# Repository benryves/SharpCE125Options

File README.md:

# Sharp CE-125 Options

This repository describes three "option" devices that plug into the expansion port of the Sharp CE-125 printer and cassette interface:

* [ROM](rom): A simple cartridge that contains a BASIC program that can be loaded onto the pocket computer via the ROM command.
* [Keyboard](keyboard): A PS/2 keyboard adaptor that allows you to type on the pocket computer from an external keyboard.
* [Serial](serial): An RS-232 interface that lets you transfer data between the pocket computer and another RS-232 device.

These all rely on undocumented keywords implemented in the pocket computer's ROM,
and are fully compatible with the PC-1251 and mostly compatible with the PC-1245.

Later pocket computers that removed these undocumented keywords (such as the PC-1246 and PC-1248) are unfortunately not supported.

These devices are intentionally kept simple to try to keep them in line with how I imagined the original devices would have worked,
had they been released.
For example, the RS-232 serial interface's BASIC keywords are very similar to those of the CE-158 RS-232 interface for the PC-1500,
so I tried to maintain as much compatibility with the CE-158's operation as possible.

These devices all use a [common library](lib) and so it should be possible to build a device that hooks into the same BASIC keywords,
but performs some other function; for example, using `INSTAT` and `OUTSTAT` to control 8 general I/O lines instead of making them control
RS-232 handshaking lines, or using the cassette output redirection from `CSAVE` to allow programs to be saved to the ROM module.

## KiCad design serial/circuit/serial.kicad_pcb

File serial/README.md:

# RS-232 serial interface

> [!WARNING]
> The SHARP CE-125's power supply has a reversed polarity, i.e. the power supply pin VP has a _negative_ voltage relative to the ground pin GND.
> To keep the serial interface's circuit simple, it's connected "backwards" to the power supply, with the result that the serial port's GND is not at the same potential as the CE-125's other ground connections.  
> Therefore, care must be taken to ensure that the serial port ground and CE-125 ground are not shorted together, for example by plugging the serial port and cassette interface input socket to the same device at the same time, or by splitting a power supply and powering both the CE-125 and a serial device from the same power supply instead of using separate, isolated power supplies.  
> A low-current fuse **must** be included in the serial interface to protect the CE-125 against damage from such short-circuits, as the rechargeable battery pack can deliver a significant amount of current.

## Specifications

* **Baud rate:** 110, 300 or 1200 as standard via SETCOM; 75, 600, 2400, 4800 and 9600 via custom code.
* **Data bits:** 7 or 8.
* **Parity:** None, even or odd.
* **Stop bits:** 1 or 2.
* **Connector:** DE-9 wired as DTE.

## Command reference table

* **Statements:**
  * SETCOM, OUTSTAT
  * INPUT, INPUT #
  * PRINT, PRINT #
  * LPRINT, LLIST
  * CLOAD, CSAVE
  * KEY
* **Functions:**
  * COM$, INSTAT

|Command|Example     |Function                                                            |
|:------|:-----------|:-------------------------------------------------------------------|
|SETCOM |SETCOM 300,N,8,1,PO|Sets communication parameters and device redirection.        |
|       |SETCOM OFF  |Resets device redirection.                                          |
|OUTSTAT|OUTSTAT 0   |Sets status of RS-232 output signals.                               |
|INPUT  |INPUT "A=";A|Loads the variable with ASCII data input from the RS-232 port.      |
|INPUT #|INPUT #A    |Loads the variable with binary data input from the RS-232 port.     |
|PRINT  |PRINT 123   |Sends data through the RS-232 port in ASCII format.                 |
|PRINT #|PRINT #A    |Sends data through the RS-232 port in binary format.                |
|LPRINT |LPRINT 123  |Sends data through the RS-232 port in ASCII format.                 |
|LLIST  |LLIST 10,100|Lists the program through the RS-232 port in ASCII format.          |
|CLOAD  |CLOAD       |Loads a program from the RS-232 port in binary format.              |
|CSAVE  |CSAVE       |Saves a program through the RS-232 port in binary format.           |
|KEY    |KEY ON      |Accepts keyboard input from ASCII data sent through the RS-232 port.|
|       |KEY OFF     |Disables keyboard input through the RS-232 port.                    |
|COM$   |COM$        |Current communication parameters as a character string.             |
|INSTAT |INSTAT      |Retrieves current status of RS-232 input signals.                   |

## Pin assignment

|Pin No.|Item               |Symbol|In/Out|Remarks                          |
|:-----:|:------------------|:----:|:----:|:--------------------------------|
|   1   |Carrier Detect     |  CD  |  In  |ON when a cable isn't connected. |
|   2   |Receive Data       |  RD  |  In  |                                 |
|   3   |Transmit Data      |  TD  |  Out |                                 |
|   4   |Data Terminal Ready|  DTR |  Out |OFF on initial power up.         |
|   5   |Signal Ground      |  SG  |      |                                 |
|   6   |Data Set Ready     |  DSR |  In  |ON when a cable isn't connected. |
|   7   |Request-To-Send    |  RTS |  Out |OFF on initial power up.         |
|   8   |Clear-To-Send      |  CTS |  In  |OFF when a cable isn't connected.|
|   9   |Ring Indicator     |  RI  |  In  |ON when a cable isn't connected. |

The RS-232 interface is wired as DTE (data terminal equipment) which means it can be connected to devices wired as DCE (data communication equipment) such as a modem or a printer with a straight-through cable.
To connect it to another DTE (such as directly to another different computer) you will need to use a null modem cable between the two devices.

## Handshaking

The interface will not transmit data unless CD, DSR and CTS are all ON.
CD and DSR are pulled high to the ON state when a cable is not connected, so will not inhibit communication if they are missing however CTS is pulled low to the OFF state and so must be driven high.

When the interface is first powered up both DTR and RTS are in the OFF state, and this will likely prevent the connected device from sending data to the interface.
DTR and RTS can be switched to the ON state by using the OUTSTAT 0 command.

The interface has a small data receive buffer and will automatically switch RTS to the OFF state when this starts to fill up.
It will then automatically switch RTS back to the ON state once the received data has been transferred from the interface to the computer.

## Character encoding

Data transferred between the computer and the interface always uses the internal character encoding specific to the SHARP Pocket Computer.
These characters are converted to and from ASCII when sent or received over the RS-232 port when used with certain commands:

* **ASCII encoding:**
  * INPUT, PRINT
  * LPRINT, LLIST
  * KEY
* **SHARP Pocket Computer internal encoding:**
  * INPUT #, PRINT #
  * CLOAD, CSAVE

`CR` (13, &0D) is used as a line/data terminator in both situations.

The SHARP Pocket Computer does support converting its internal character values to and from ASCII using the ASC and CHR$ functions, however there are some differences that are noted here:

|Code (Decimal)|Code (Hex)|ASCII|SHARP|
|:------------:|:--------:|:---:|:---:|
|      39      |    &27   |  '  | INS |
|      91      |    &5B   |  \[ |  √  |
|      92      |    &5C   |  \\ |  ¥  |
|      93      |    &5D   |  \] |  π  |
|      96      |    &60   |  `  |  𝐄  |

## Principle of operation

The serial interface is designed around redirecting certain operations that would normally exchange data with another device (such as the keyboard, screen, printer or cassette) to instead exchange data via the RS-232 port.

The SETCOM command is used to set this up. It first takes a list of communication parameters (such as baud rate and number of data bits) and then a list of devices to redirect.

For example,

> SETCOM 300,N,8,1,CI,CO

sets the communication parameters to 300 baud, no parity, 8 data bits, 1 stop bit and enables redirection of Cassette Input and Cassette Output.
From this point, any operations that would have normally transferred data to or from the tape cassette will instead transfer the data via the serial port using the specified communication parameters.

The five devices that can be redirected are as follows:

|Symbol|Item           |In/Out|Affected commands|
|:----:|:--------------|:----:|:----------------|
|  KI  |Keyboard Input |  In  |INPUT            |
|  DO  |Display Output |  Out |PRINT            |
|  PO  |Printer Output |  Out |LPRINT, LLIST    |
|  CI  |Cassette Input |  In  |CLOAD, INPUT #   |
|  CO  |Cassette Output|  Out |CSAVE, PRINT #   |

Individual communication parameters can be omitted (the comma will remain) in which case the default values will be used (300 baud, No parity, 8 data bits, 1 stop bit).

At least one device must be specified. To disable the serial interface, use SETCOM OFF.

## BASIC programming reference

### SETCOM

Used to set communication parameters such as baud rate and number of data bits as well as which I/O devices should be redirected to or from the serial interface.

> SETCOM 300,N,8,1,CI,CO

* **Baud rate:** 110, 300, 1200.
* **Parity:** N (None), E (Even), O (Odd).
* **Data bits:** 7, 8.
* **Stop bits:** 1, 2.
* **Device:** KI (Keyboard Input), DO (Display Output), PO (Printer Output), CI (Cassette Input), CO (Cassette Output).

Default communication parameters are 300 baud, no parity, 8 data bits and 1 stop bit.

You must always specify at least one device to redirect.

> SETCOM OFF

Disables device redirection.

### COM$

Retrieves a character string that contains the last set of communication parameters and redirected devices.

At power on:

> 300,N,8,1

After executing SETCOM 1200,E,7,1,PO:

> 1200,E,7,1,PO

### OUTSTAT

Used to set the state of the handshaking signal lines (RTS, DTR).

> OUTSTAT 0

The handshaking signal lines are assigned as follows:

|Value              |Item               |Symbol|In/Out|
|:-----------------:|:------------------|:----:|:----:|
|2<sup>5</sup> = &20|Ring Indicator     |  RI  |  In  |
|2<sup>4</sup> = &10|Data Set Ready     |  DSR |  In  |
|2<sup>3</sup> = &08|Carrier Detect     |  CD  |  In  |
|2<sup>2</sup> = &04|Clear-To-Send      |  CTS |  In  |
|2<sup>1</sup> = &02|Request-To-Send    |  RTS |  Out |
|2<sup>0</sup> = &01|Data Terminal Ready|  DTR |  Out |

* 0 bit: ON, high level, V+ at connector.
* 1 bit: OFF, low level, V- at connector.

RTS and DTR are 1 at power on, putting them in the OFF state.

### INSTAT

Used to get the state of the handshaking signal lines. The values returned by this have the same pin assignments as documented above for OUTSTAT.

### INPUT

When the KI (Keyboard Input) device has been redirected, this command reads ASCII text from the serial port into the specified variables. Data is read from the serial port until `CR` is received, and a comma is treated as a data separator.

> 10 OUTSTAT 0  
> 20 SETCOM 300,N,8,1,KI  
> 30 INPUT "IN EXCURSION OF KI",A,B$,C  
> 40 PRINT A;B$;C  
> 50 END

|Key operation|Display           |Serial input data              |
|:------------|:-----------------|:------------------------------|
|RUN `ENTER`  |IN EXCURSION OF KI|1+2, RS-232C `CR`<br>SIN30 `CR`|
|             |3.RS-232C0.5      |                               |

### LPRINT

When the PO (Printer Output) device has been redirected, this command sends ASCII text to the serial port.

> LPRINT "THE ANSWER IS ";A

Numeric values will be formatted according to the specified USING format.

### LLIST

When the PO (Printer Output) device has been redirected, this command lists the current program as ASCII text to the serial port.

> LLIST

LLIST on its own lists the entire program.

> LLIST start,end

LLIST with a start and end parameter lists the program between the lines "start" and "end".

### PRINT

When the DO (Display Output) device has been redirected, this command sends ASCII text to the serial port.

> PRINT "RS-232C"

Numeric values will not be formatted according to the specified USING format.

### CSAVE

When the CO (Cassette Output) device has been redirected, this command sends the current program in binary format to the serial port.

> CSAVE

A `CR` terminator follows the program data. Filenames and machine code programs are not supported.

### CLOAD

When the CI (Cassette Input) device has been redirected, this command loads a program in binary format from the serial port.

A `CR` terminator must follow the program data to signify the end of the program. Filenames and machine code programs are not supported.

### PRINT \#

When the CO (Cassette Output) device has been redirected, this command sends variable data in binary format to the serial port.

> PRINT #

When used alone all of the preallocated variables (A-Z) and the array A() variables with subscript numbers greater than 26 are transmitted.

> PRINT #X

When a preallocated variable or array A() variable is specified then that variable and all subsequent variables (including array A() variables with subscript numbers greater than 26) are transmitted.

> PRINT #B(\*)

When a user-dimensioned array variable is specified with an asterisk enclosed in the parentheses then the contents of that specific array variable are transmitted.
You cannot transmit a single element of an array.

> PRINT #X,B(\*),F$(\*)

More than one starting variable can be included in the variable list.
A `CR` terminator is sent after all variables listed in the PRINT # command have been transmitted.

As `CR` may appear within the data itself it's not sufficient to record data from the serial port until a `CR` terminator is seen.
Instead, the first five bytes sent over the serial port can be used to calculate the total length of the data:

#### Pre-allocated variables or array A()

The sequence &FE, &00, &00, &00, &00 is sent over the serial port, followed by a number of 8-byte variables.
After the last 8-byte variable has been sent, a terminator byte of &0F is sent.

#### User-dimensioned array variables

* Two bytes are sent indicating the length of the following data in bytes, most significant byte first.
* One byte is sent containing the upper bound of the array's second dimension (0 for single-dimension arrays).
* One byte is sent containing the upper bound of the array's first dimension.
* One byte is sent containing the size of each array element in bytes (8 for numeric variables, 16 for character strings unless modified with \* when dimensioning the array).

The array's element data then follows.
As the size of the array is explicitly recorded in the above five-byte header, there is no need for a terminator byte as with the pre-allocated variables.

### INPUT \#

When the CI (Cassette Input) device has been redirected, this command receives variable data in binary format from the serial port.

> INPUT #

When used alone the preallocated variables are loaded started from A.

> INPUT #X

When a preallocated variable or array A() variable is specified then variables are loaded starting from the specified variable.

> INPUT #B(*)

When a user-dimensioned array variable is specified with an asterisk enclosed in the parentheses then the contents of that specific array variable is loaded.
You cannot load a single element of an array.

> INPUT #X,B(\*),F$(\*)

More than one starting variable can be included in the variable list.
A `CR` terminator needs to be sent after all variables listed in the INPUT # command to end the transfer.

### KEY

The SHARP Pocket Computer can also accept keyboard input from the RS-232 port.
Unlike the INPUT command this will work more generally; for example, you could use this to load a BASIC program onto the computer that was stored as an ASCII text file.

> KEY ON

After executing the KEY ON command the computer will constantly check for incoming key presses from the RS-232 port as well as its own keyboard.

> KEY OFF

The KEY OFF command tells the computer to stop check for incoming key presses from the RS-232 port.

## Configuration variables

The communication parameters and device redirection state are stored in two variables in the computer's memory.

The bit array for redirected devices can be found at address &C6B7:

|Symbol|Value|Item           |In/Out|Affected commands|
|:----:|:---:|:--------------|:----:|:----------------|
|  KI  | &01 |Keyboard Input |  In  |INPUT            |
|  DO  | &02 |Display Output |  Out |PRINT            |
|  PO  | &04 |Printer Output |  Out |LPRINT, LLIST    |
|  CI  | &08 |Cassette Input |  In  |CLOAD, INPUT #   |
|  CO  | &10 |Cassette Output|  Out |CSAVE, PRINT #   |

This value is checked when any of the affected commands is used to determine whether to redirect the data via the serial port instead of the default device.
This means you can enable or disable device redirection without using SETCOM, just POKE.
For example, to redirect cassette devices CI and CO:

> POKE &C6B7,&08 OR &10

The communication parameters can be found at address &C6B8:

|Parameter       |Value|Bits|
|:---------------|:---:|----:
|Baud rate (300) | &00 | 1~0|
|Baud rate (110) | &01 | 1~0|
|Baud rate (1200)| &02 | 1~0|
|Parity (None)   | &00 | 3~2|
|Parity (Even)   | &04 | 3~2|
|Parity (Odd)    | &08 | 3~2|
|Data bits (8)   | &00 |   4|
|Data bits (7)   | &10 |   4|
|Stop bits (1)   | &00 |   5|
|Stop bits (2)   | &20 |   5|

The communication parameters need to be sent to the serial interface for them to take effect and so POKEing a new value into the computer's memory is not enough to change them.
However, a side-effect of SETCOM OFF is that it clears the device redirection bit array at &C6B7 and then sends this new zero value to the serial interface along with the current communication parameters at &C6B8.
This means you can POKE a custom value to &C6B8, send it to the serial interface with SETCOM OFF, and then enable redirection for the desired devices by POKEing the appropriate value to &C6B7.

This technique has been used to add five additional baud rates to the three currently supported by SETCOM, giving eight in total:

|Parameter       |Value|Bits |
|:---------------|:---:|----:|
|Baud rate (300) | &00 |6,1~0|
|Baud rate (110) | &01 |6,1~0|
|Baud rate (1200)| &02 |6,1~0|
|Baud rate (600) | &03 |6,1~0|
|Baud rate (2400)| &40 |6,1~0|
|Baud rate (75)  | &41 |6,1~0|
|Baud rate (9600)| &42 |6,1~0|
|Baud rate (4800)| &43 |6,1~0|

A sample program that enables one of the additional baud rates is shown below:

> 10 SETCOM,,,2,CI,CO  
> 20 B=&42: GOSUB "BAUD"  
> 30 PRINT COM$  
> 40 END  
> 100 "BAUD": POKE &C6B8,B OR (&BC AND PEEK &C6B8)  
> 110 D= PEEK &C6B7: SETCOM OFF  
> 120 POKE &C6B7,D: RETURN

Line 10 sets the communication parameters using SETCOM.
Line 20 sets B to &42 (the value for 9600 baud from the table above) and calls the BAUD subroutine to change the baud rate.
Line 30 then shows the updated communication parameters on the display, confirming the switch to 9600 baud.

The BAUD subroutine starts on line 100.
It first updates the baud rate bits in &C6B8, then backs up the device redirection bit array from &C6B7.
SETCOM OFF is then used to send the updated communication parameters to the serial interface.
Finally, the old device redirection bit array is restored to &C6B7 to re-enable any redirected devices that were disabled by SETCOM OFF.

## Use with the SHARP PC-1245

The SETCOM command is disabled on the SHARP PC-1245, which means it is not possible to use it to configure the communication parameters or redirect devices to the serial port.

You can still enable device redirection by POKEing the appropriate configuration value into the bit array at address &C6B7.
For example, to redirect cassette devices CI and CO:

> POKE &C6B7,&08 OR &10

It should be possible to call into the ROM to replicate the behaviour of the missing SETCOM, however.
The PC-1251 instruction manual contains an example on how to send characters directly to the printer (page 221, "Printout of special characters").
This does point out that different ROM revisions have different addresses for the used routines, and it's likely that the same applies to the PC-1245.

As such, I cannot present a one-size-fits-all solution, but this routine works on my particular PC-1245:

|Assembly           |Machine code (Hex)|Machine code (Decimal)|
|:------------------|:-----------------|:---------------------|
|LIA 70	            |&02, &70          |2, 112                |
|CALL PCU_WRITE_BYTE|&78, &7D, &6F     |120, 125, 111         |
|LIDP C6B8          |&10, &C6, &B8     |16, 198, 184          |
|LDD	               |&57               |87                    |
|CALL PRINT_QUEUE   |&78, &7B, &91     |120, 123, 145         |
|CAL SETDEV_PTR	    |&F1, &66          |241, 102              |
|LDD	               |&57	              |87                    |
|JP 6C1E           	|&79, &6C, &1E     |121, 108, 30          |

When included in a BASIC program, the routine might look like this:

> 10 DIM Z$(1)*6  
> 20 POKE &C5BE,2,112,120,125,111,16,198,184,87,120,123,145,241,102,87,121,108,30  
> 30 POKE &C6B7,&04,&42  
> 40 CALL &C5BE  
> 50 PRINT COM$

Line 30 sets the redirected device to PO (Printer Output) and the communication parameters to 9600 8N1 so the program should display "9600,N,8,1,PO" on the computer's LCD.

## Quirks and limitations

The LPRINT and PRINT commands still assume the printer is 24 characters wide.
Printing a single numeric value will align it inside a 24 character field; printing two values with a comma between them will align them inside 12 character fields.

Program listings printed with LLIST are also affected by the 24 character limit.
Individual lines are wrapped to avoid breaking a keyword across multiple lines; additional spaces are printed at the end of each wrapped line to advance the cursor to the next line and additional spaces are printed at the start of each wrapped line to intend them.
The serial interface does attempt to undo this hard wrapping but it's far from perfect.

Not all cassette-related commands are redirected: CLOAD M, CSAVE M and MERGE will still access the cassette instead of the serial interface.

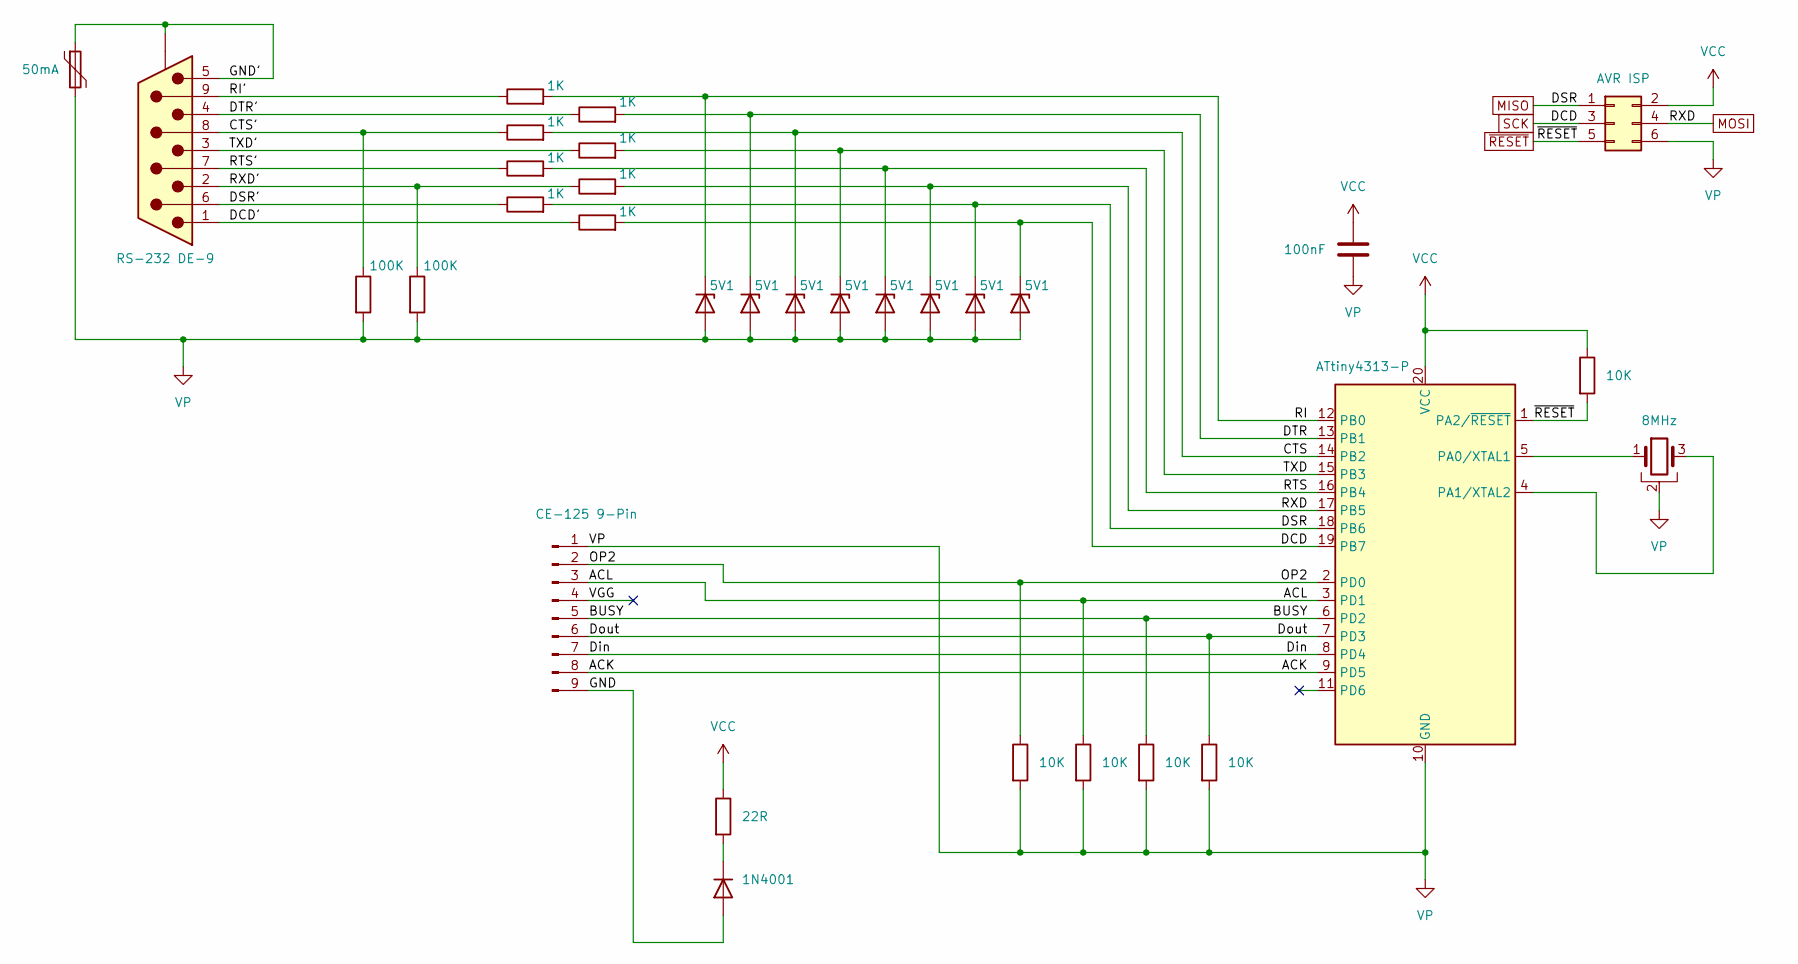
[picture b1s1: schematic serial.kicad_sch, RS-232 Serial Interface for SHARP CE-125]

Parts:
C1: 100nF; C_Disc_D3.0mm_W1.6mm_P2.50mm
D1, D2, D3, D4, D5, D6, D7, D8: 5V1; D_DO-34_SOD68_P5.08mm_Horizontal
D9: 1N4001; D_DO-34_SOD68_P7.62mm_Horizontal
F1: 50mA; C_Disc_D4.7mm_W2.5mm_P5.00mm
J1: CE-125 9-Pin; PinHeader_1x09_P2.54mm_Horizontal
J2: RS-232 DE-9; DSUB-9_Pins_Horizontal_P2.77x2.84mm_EdgePinOffset7.70mm_Hou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
J3: AVR ISP; IDC-Header_2x03_P2.54mm_Vertical
R1, R2, R3, R4, R13: 10K; R_Axial_DIN0204_L3.6mm_D1.6mm_P7.62mm_Horizontal
R5, R6, R7, R8, R9, R10, R11, R12: 1K; R_Axial_DIN0204_L3.6mm_D1.6mm_P7.62mm_Horizontal
R15, R16: 100K; R_Axial_DIN0204_L3.6mm_D1.6mm_P7.62mm_Horizontal
R18: 22R; R_Axial_DIN0204_L3.6mm_D1.6mm_P7.62mm_Horizontal
U1: ATtiny4313-P; DIP-20_W7.62mm
Y1: 8MHz; Resonator-3Pin_W8.0mm_H3.5mm

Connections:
/ACK: J1.8, U1.9 (PD5)
/ACL: J1.3, R2.1, U1.3 (PD1)
/BUSY: J1.5, R3.1, U1.6 (PD2)
/CTS: D3.1 (K), R6.2, U1.14 (PB2)
/CTS': J2.8, R6.1, R15.1
/DCD': J2.1, R12.1
/DSR': J2.6, R8.1
/DTR: D2.1 (K), R9.2, U1.13 (PB1)
/DTR': J2.4, R9.1
/Din: J1.7, U1.8 (PD4)
/Dout: J1.6, R4.1, U1.7 (PD3)
/GND: D9.2 (A), J1.9
/GND': F1.1, J2.0, J2.5
/OP2: J1.2, R1.1, U1.2 (PD0)
/RI: D1.1 (K), R5.2, U1.12 (PB0)
/RI': J2.9, R5.1
/RTS: D5.1 (K), R7.2, U1.16 (PB4)
/RTS': J2.7, R7.1
/RXD': J2.2, R11.1, R16.1
/TXD: D4.1 (K), R10.2, U1.15 (PB3)
/TXD': J2.3, R10.1
/VGG: J1.4
MISO: D7.1 (K), J3.1, R8.2, U1.18 (PB6)
MOSI: D6.1 (K), J3.4, R11.2, U1.17 (PB5)
unnamed: D9.1 (K), R18.2
unnamed: U1.5 (PA0/XTAL1), Y1.1
unnamed: U1.4 (PA1/XTAL2), Y1.3
SCK: D8.1 (K), J3.3, R12.2, U1.19 (PB7)
VCC: C1.1, J3.2, R13.1, R18.1, U1.20 (VCC)
VP: C1.2, D1.2 (A), D2.2 (A), D3.2 (A), D4.2 (A), D5.2 (A), D6.2 (A), D7.2 (A), D8.2 (A), F1.2, J1.1, J3.6, R1.2, R2.2, R3.2, R4.2, R15.2, R16.2, U1.10 (GND), Y1.2
~RESET: J3.5, R13.2, U1.1 (PA2/~RESET)

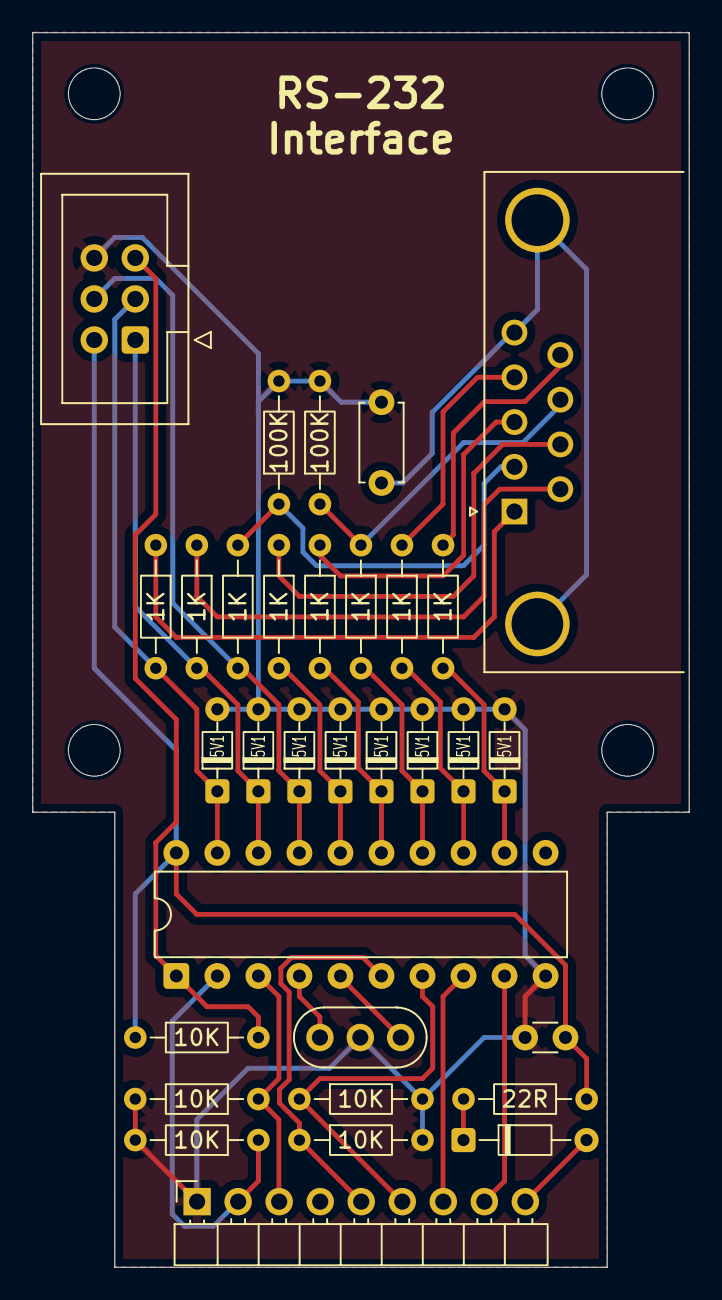
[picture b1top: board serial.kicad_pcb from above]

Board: 2 copper layers, 40.6 x 76.4 mm, 36 parts (0 on the bottom side), 30 nets.

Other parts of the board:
*: MountingHole_3.2mm_M3
*#2, *#3, *#4: MountingHole_3.2mm_M3

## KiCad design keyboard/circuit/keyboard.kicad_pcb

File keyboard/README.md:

# PS/2 keyboard interface

This interface allows you to type text into your SHARP Pocket Computer using an external PS/2 keyboard.

## Command reference table

* **Statements:**
  * KEY

|Command|Example     |Function                                                            |
|:------|:-----------|:-------------------------------------------------------------------|
|KEY    |KEY ON      |Accepts keyboard input from the keyboard connected to the PS/2 port.|
|       |KEY OFF     |Disables keyboard input through the PS/2 port.                      |

## Special keys

Certain special keys are present on the SHARP Pocket Computer keyboard that are not commonly found on PS/2 keyboards.
These keys have generally been remapped to equivalents based on the ASCII code assignments used by the Pocket Computer:
for example, ASC"√" yields 91 on the SHARP Pocket Computer which normally corresponds to the [ character in ASCII,
and so pressing [ on the PS/2 keyboard produces a √ symbol on the Pocket Computer.

|SHARP keyboard|PS/2 keyboard|
|:------------:|:-----------:|
|       √      |     \[      |
|       ¥      |     \\      |
|       π      |     \]      |
|       𝐄      |      `      |
|      CL      |     Esc     |
|      CA      |  Shift+Esc  |
|     BRK      | Pause/Break |
|     P↔NP     | Print Screen|

## Shortcuts

The SHARP Pocket Computer has two sets of keyboard shortcuts:
labelled programs that can be run by pressing DEF and then a key,
or a string that can be entered by pressing SHIFT and then a key.

These shortcuts are accessible when using the PS/2 keyboard,
using Ctrl+key instead of DEF then key for labelled programs and
Shift+key instead of SHIFT then key for reserve mode strings.

Normally these shortcuts are only avaiable for the alphabetic keys in the bottom two rows of the keyboard along with SPC and  =,
however when using a PS/2 keyboard many more keys can be redefined in this way.

The Q and T keys cannot be used as shortcuts.

### Labelled programs (DEF)

Label the start of a program's line in memory with a single-character shortcut key in quotes, for example:

```
10:"A":PRINT "FIRST"
20:END
80:"B":PRINT "SECOND"
90:END
```

Pressing Ctrl+A will run the program starting from line 10 and pressing Ctrl+B will run the program starting from line 80.

The function keys F1 to F9 and F10 can be also used to jump to the labelled programs "1" to "9" and "0" without pressing the Ctrl key.

### Reserve mode (SHIFT)

Reserve mode strings can be entered and defined for the alphabetic keys A-Z with the exception of Q and T;
in addition, reserve mode strings can be assigned to the = key and the SPC key.

For Pocket Computers that don't have a user-defineable reserve mode (such as the PC-1245)
these keys will instead type the shortcut printed above the key.

As the = key is normally used to type a + sign when the Shift key is held,
Shift+Enter is used to enter the reserve mode string assigned to =.

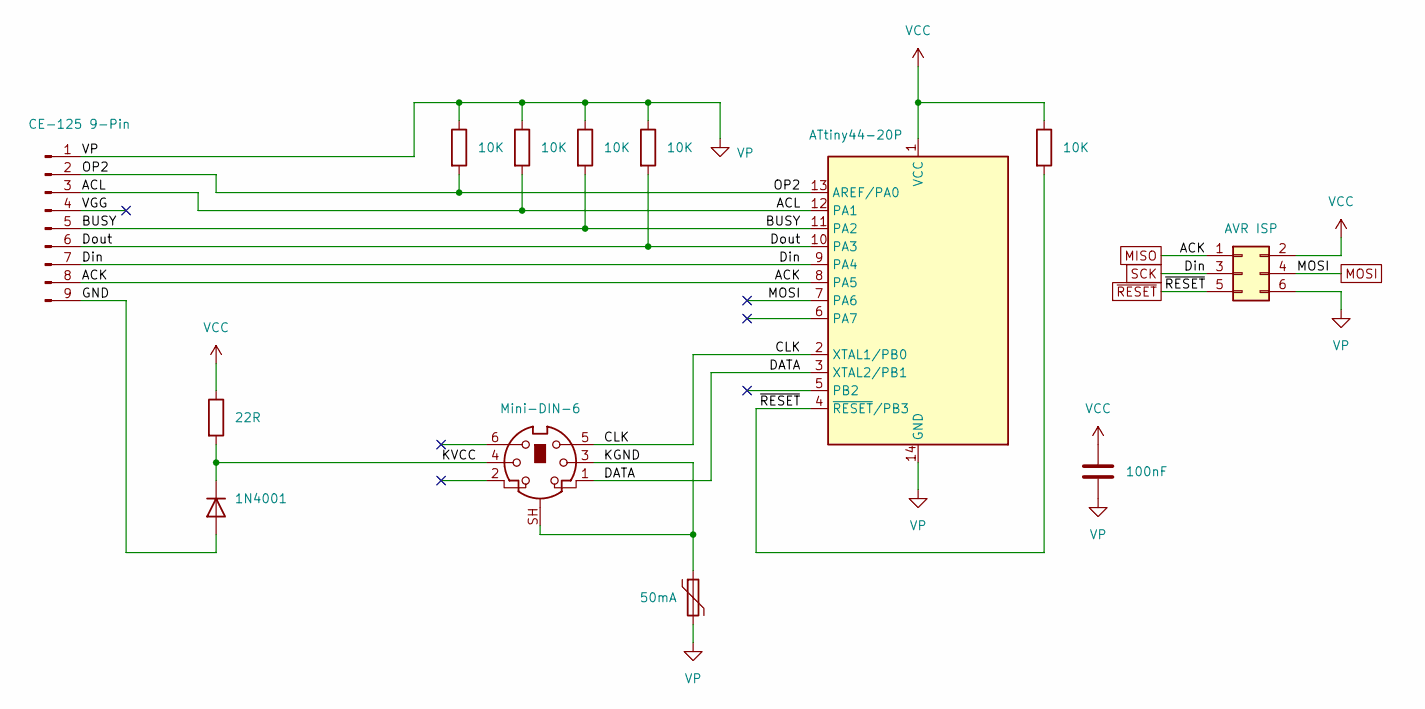
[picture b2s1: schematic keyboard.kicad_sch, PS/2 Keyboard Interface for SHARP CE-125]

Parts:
C1: 100nF; C_Disc_D3.0mm_W1.6mm_P2.50mm
D9: 1N4001; D_DO-34_SOD68_P7.62mm_Horizontal
F2: 50mA; C_Disc_D4.7mm_W2.5mm_P5.00mm
J1: CE-125 9-Pin; PinHeader_1x09_P2.54mm_Horizontal
J2: AVR ISP; IDC-Header_2x03_P2.54mm_Vertical
J3: Mini-DIN-6; Mini_DIN_round_6_canned
R1, R2, R3, R4, R13: 10K; R_Axial_DIN0204_L3.6mm_D1.6mm_P7.62mm_Horizontal
R18: 22R; R_Axial_DIN0204_L3.6mm_D1.6mm_P7.62mm_Horizontal
U2: ATtiny44-20P; DIP-14_W7.62mm

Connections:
/ACL: J1.3, R2.2, U2.12 (PA1)
/BUSY: J1.5, R3.2, U2.11 (PA2)
/CLK: J3.5, U2.2 (XTAL1/PB0)
/DATA: J3.1, U2.3 (XTAL2/PB1)
/Dout: J1.6, R4.2, U2.10 (PA3)
/GND: D9.2 (A), J1.9
/KGND: F2.1, J3.3, J3.SH
/KVCC: D9.1 (K), J3.4, R18.2
/OP2: J1.2, R1.2, U2.13 (AREF/PA0)
/VGG: J1.4
MISO: J1.8, J2.1, U2.8 (PA5)
MOSI: J2.4, U2.7 (PA6)
SCK: J1.7, J2.3, U2.9 (PA4)
VCC: C1.1, J2.2, R13.1, R18.1, U2.1 (VCC)
VP: C1.2, F2.2, J1.1, J2.6, R1.1, R2.1, R3.1, R4.1, U2.14 (GND)
~RESET: J2.5, R13.2, U2.4 (~RESET/PB3)

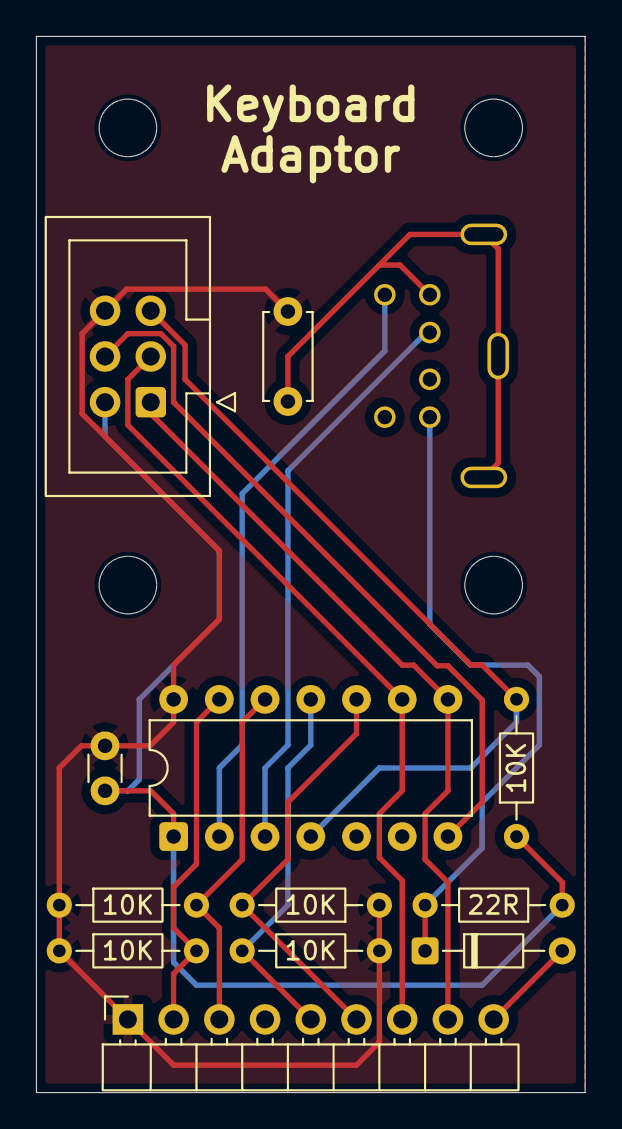
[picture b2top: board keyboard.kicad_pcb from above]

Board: 2 copper layers, 30.5 x 58.7 mm, 17 parts (0 on the bottom side), 15 nets.

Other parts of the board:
MountingHole: MountingHole_3.2mm_M3
MountingHole#2, MountingHole#3, MountingHole#4: MountingHole_3.2mm_M3

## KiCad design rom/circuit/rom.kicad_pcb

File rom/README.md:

# ROM program module

A BASIC program can be stored on a program module and loaded into the computer's memory with the ROM statement.

## Command reference table

* **Statements:**
  * ROM

|Command|Example     |Function                                        |
|:------|:-----------|:-----------------------------------------------|
|ROM    |ROM         |Loads the program from the connected ROM module.|

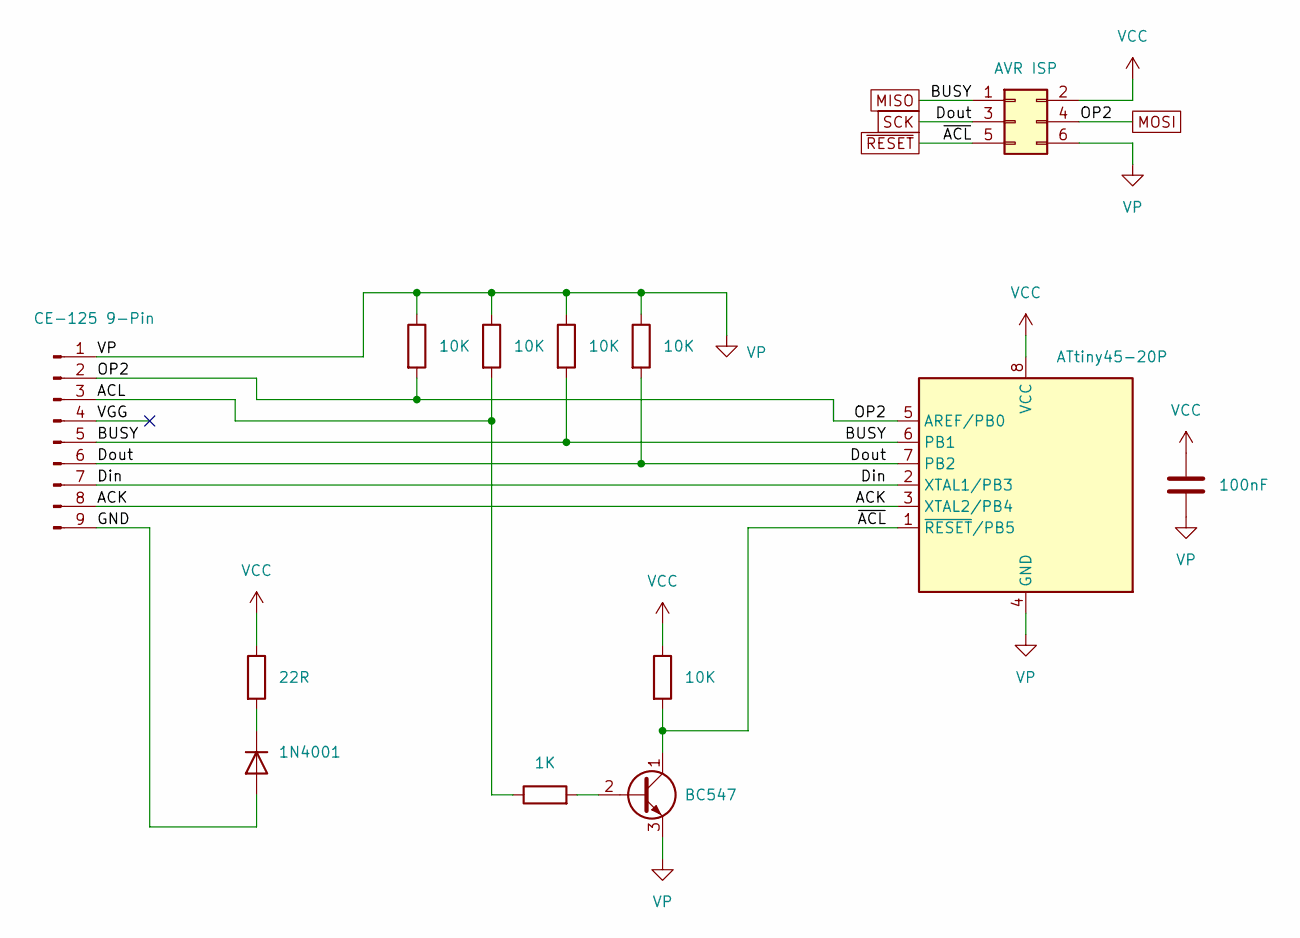
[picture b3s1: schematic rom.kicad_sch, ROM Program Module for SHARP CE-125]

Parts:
C1: 100nF; C_Disc_D3.0mm_W1.6mm_P2.50mm
D1: 1N4001; D_DO-35_SOD27_P7.62mm_Horizontal
J1: CE-125 9-Pin; PinHeader_1x09_P2.54mm_Horizontal
J2: AVR ISP; IDC-Header_2x03_P2.54mm_Vertical
Q1: BC547; TO-92_Inline
R1: 22R; R_Axial_DIN0204_L3.6mm_D1.6mm_P7.62mm_Horizontal
R2, R3, R5, R6, R7: 10K; R_Axial_DIN0204_L3.6mm_D1.6mm_P7.62mm_Horizontal
R4: 1K; R_Axial_DIN0204_L3.6mm_D1.6mm_P7.62mm_Horizontal
U1: ATtiny45-20P; DIP-8_W7.62mm

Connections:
/ACK: J1.8, U1.3 (XTAL2/PB4)
/ACL: J1.3, R3.2, R4.1
/Din: J1.7, U1.2 (XTAL1/PB3)
/GND: D1.2 (A), J1.9
/VGG: J1.4
MISO: J1.5, J2.1, R5.2, U1.6 (PB1)
MOSI: J1.2, J2.4, R2.2, U1.5 (AREF/PB0)
unnamed: D1.1 (K), R1.2
unnamed: Q1.2 (B), R4.2
SCK: J1.6, J2.3, R6.2, U1.7 (PB2)
VCC: C1.1, J2.2, R1.1, R7.1, U1.8 (VCC)
VP: C1.2, J1.1, J2.6, Q1.3 (E), R2.1, R3.1, R5.1, R6.1, U1.4 (GND)
~RESET: J2.5, Q1.1 (C), R7.2, U1.1 (~RESET/PB5)

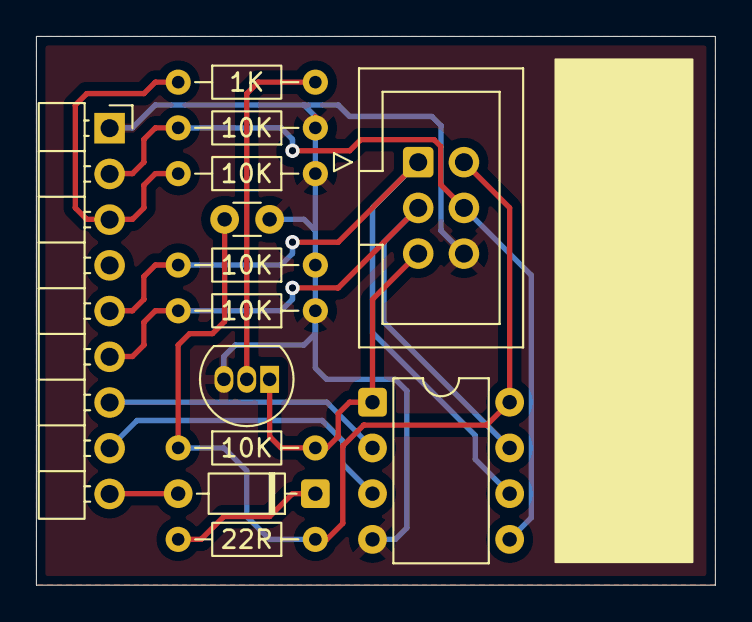
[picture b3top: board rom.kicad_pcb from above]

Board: 2 copper layers, 37.7 x 30.5 mm, 13 parts (0 on the bottom side), 12 nets.

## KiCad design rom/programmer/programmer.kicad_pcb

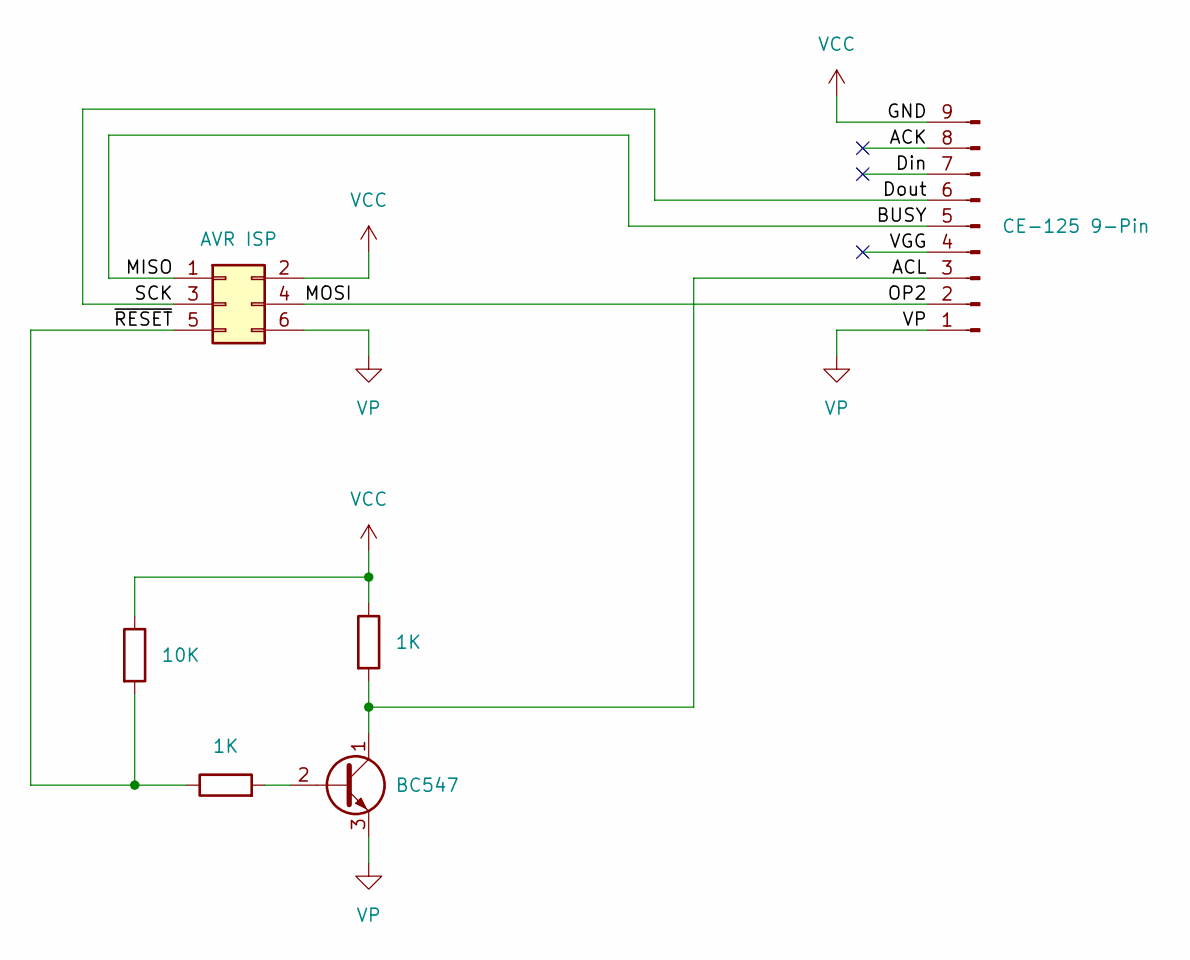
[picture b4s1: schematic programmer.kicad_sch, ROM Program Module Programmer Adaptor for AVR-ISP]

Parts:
J1: CE-125 9-Pin; PinSocket_1x09_P2.54mm_Horizontal
J2: AVR ISP; IDC-Header_2x03_P2.54mm_Vertical
Q1: BC547; TO-92_Inline
R1: 10K; R_Axial_DIN0204_L3.6mm_D1.6mm_P7.62mm_Horizontal
R4, R7: 1K; R_Axial_DIN0204_L3.6mm_D1.6mm_P7.62mm_Horizontal

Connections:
/ACK: J1.8
/ACL: J1.3, Q1.1 (C), R7.2
/BUSY: J1.5, J2.1
/Din: J1.7
/Dout: J1.6, J2.3
/MOSI: J1.2, J2.4
/VGG: J1.4
/~RESET: J2.5, R1.2, R4.1
unnamed: Q1.2 (B), R4.2
VCC: J1.9, J2.2, R1.1, R7.1
VP: J1.1, J2.6, Q1.3 (E)

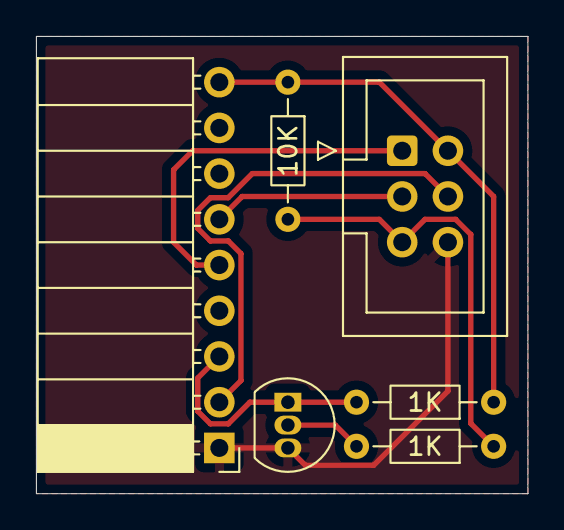
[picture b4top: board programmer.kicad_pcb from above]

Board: 2 copper layers, 27.3 x 25.4 mm, 6 parts (0 on the bottom side), 8 nets.

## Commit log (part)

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2026-01-26 Added the crude start of the serial interface
    No Sharp-specific code is implemented yet, just a simple UART based on some existing ATtiny13 code.
2026-01-26 Added basic Sharp protocol handler
    It can detect the ACL condition and receive bytes. Not very robust (no timeout handling) but a good start.
2026-01-26 Added WDT-based timeout code
2026-01-26 Added INSTAT support
    This demonstrates how the send_byte() routine works.
2026-01-26 Implemented routines triggered by receiving data
2026-01-26 Implemented routines that return data
2026-01-26 Correction of some variable types
2026-01-26 Added initial rough version of the schematic
2026-01-27 Added diode and resistor on +ve power supply
2026-01-27 uart_init() now takes a baud rate
    110, 300, 600, 1200, 2400, 4800 and 9600 all appear to work.
2026-01-27 UART sends data bits, parity and stop bits
2026-01-29 Added data size+parity check for incoming data
2026-01-29 ACL empties UART send/receive buffers
2026-01-29 Moved TXD to PB3
    This matches the schematic and should be easier to wire up.
2026-01-29 Added KiCad .lck files to .gitignore
2026-01-29 Added INSTAT/OUTSTAT
    These control the status lines. DCD, DSR and RI are pulled high now by default (DCD and DSR are pulled high by the CE-158).
2026-01-30 Implemented SETCOM and COM$
2026-02-01 Refactored SHARP code into its own module
2026-02-01 Simplified external interface to code
2026-02-01 Fixed sharp_char_to_token for characters < 0x20
2026-02-01 Improved the wrapping of LLIST
    It's still a bit wonky due to the computer hard wrapping to 24 characters per line
2026-02-01 Added basic handshaking
    Data won't be sent unless CTS, DCD and DSR are active (ACL can clear this state).
2026-02-01 Added automatic RTS assertion
2026-02-01 Added a timeout for keyboard input
2026-02-02 Sleep when link is idle
    This is a bit hacky at the moment but lowers idle current from 5.56mA to 2.76mA, around half the power consumption.
2026-02-02 Moved the sleep code into sharp.c
2026-02-04 Made it possible to reject unsupported commands
    At the moment this blocks ROM; it forces a time-out on the last bit of the transfer.
2026-02-04 Added a SHARP_CONFIG to enable/disable features
2026-02-04 Include stdint.h instead stdlib.h
2026-02-04 Improved sharp_serial_data_begin()
    Now sends proper mode (previously sent receive mode when sending) and the input buffer is no longer cleared when switching to keyboard input.
2026-02-06 Corrected the pull-down resistor placement
    They should be on OP2 and ACL but not on Din and ACK.
2026-02-09 INSTAT no longer triggers sharp_serial_data_end
2026-02-09 Fixed uart_is_busy() for receiving
2026-02-09 No longer exit sharp_serial_data_end on ACL
    This was only previously needed as uart_is_busy() was returning true when the UART wasn't busy and so would lock up the interface.
2026-02-12 Added a 50mA polyfuse to serial port GND
    Serial port GND is connected to the negative side of the battery and chassis GND is connected to the positive side of the battery. Connecting serial port GND to chassis GND would short-circuit the ba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
    This isn't too far-fetched, as the cassette "in" terminal is connected to chassis GND, so connecting both cassette "in" and a serial cable at the same time to the same computer would short out the ba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
2026-02-27 Split INPUT values by ','
    The CE-158 for the PC-1500 uses ',' as a delimiter in INPUT data, so this is reflected here for consistency.
2026-02-28 Added a crude keyboard interface
    This uses code from the AVR I/O controller from my Z80 computer project. The keyboard layout returns codes which are then crudely translated to Sharp tokens; really, this should instead embed the pro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
2026-02-28 Switched to internal 8MHz RC oscillator
2026-02-28 Added a proper keyboard layout
2026-02-28 Added DEF and RSV key bindings
2026-03-01 Adapted to run on ATtiny44/84
2026-03-01 Swapped keyboard clock/data pins
    Makes for easier circuit diagram and wiring as CE-125 pins have also been flipped.
2026-03-01 Added circuit diagram for the keyboard interface
2026-03-04 Added a very crude ROM option
    This loads a "HELLO WORLD" program from an ATtiny13, but as the Sharp library takes up most of the 1KB ROM space that's all there's room for!
2026-03-04 Made char<->token utility functions optional
    This frees up a lot of ROM space.
2026-03-04 Changed sample program to A-11
    This is a more useful sample from the PC-1251 application tape.
2026-03-04 Promoted "sharp" to a shared library
2026-03-06 Moved the "keyboard" circuit out of a subfolder
2026-03-06 Added ROM program module circuit diagram
2026-03-09 Added AVR ISP to ROM schematic
2026-03-14 Designed a PCB for the ROM module
2026-03-27 Moved connector to CE-125 closer to board edge.
2026-03-27 Generated Gerber files for the ROM module
2026-03-28 Routed basic PCB for the PS/2 keyboard adaptor
2026-03-28 Tidied up PCB labels on keyboard adaptor
2026-03-28 Routed an initial PCB for the serial interface
    Very ugly at the moment and generating a lot of errors!
2026-03-28 Tidied up routing of serial interface PCB
2026-03-28 Tidied up labels
    Board now passes DRC
2026-03-28 Added copper pour and title
2026-03-29 Added programmer adaptor board for ROM
2026-03-29 Generated gerbers for all circuits
2026-03-29 Fixed pin 1 assignment in CE-125 connector
2026-04-09 Switched keyboard Makefile to ATtiny44
2026-04-09 Changed the ROM project to ATtiny85
2026-05-30 Corrected the AVR-ISP connections
    Both serial and keyboard projects had incorrect connections from the AVR-ISP to the microcontroller.
